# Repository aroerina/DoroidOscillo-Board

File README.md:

## Description
DroidOscillo KiCAD board data  
Schematic is here  
https://github.com/aroerina/DroidOscillo-Photos/blob/master/Schematic.pdf

## Building tools
KiCAD 4.0.2

## Parts description
U1 LPC4370FET100 - Main MCU.204MHz triple core(Cortex M4 + M0 * 2) and includes 80Msps ADC.  
U5 OPA4354 - Quad cmos opamp.  
U14 MCP4726A0T-E/CH - 12bit I2C DAC.  

## Related repositorys

DroidOscillo Firmware: https://github.com/aroerina/DroidOscillo-Firmaware  
DroidOscillo Android host: https://github.com/aroerina/DroidOscillo-Android_host  

## Wiki
https://github.com/aroerina/DroidOscillo-Android_host/wiki

## Licence

DroidOscillo Hardware is released under the [CC BY-NC 4.0](https://creativecommons.org/licenses/by-nc/4.0/)

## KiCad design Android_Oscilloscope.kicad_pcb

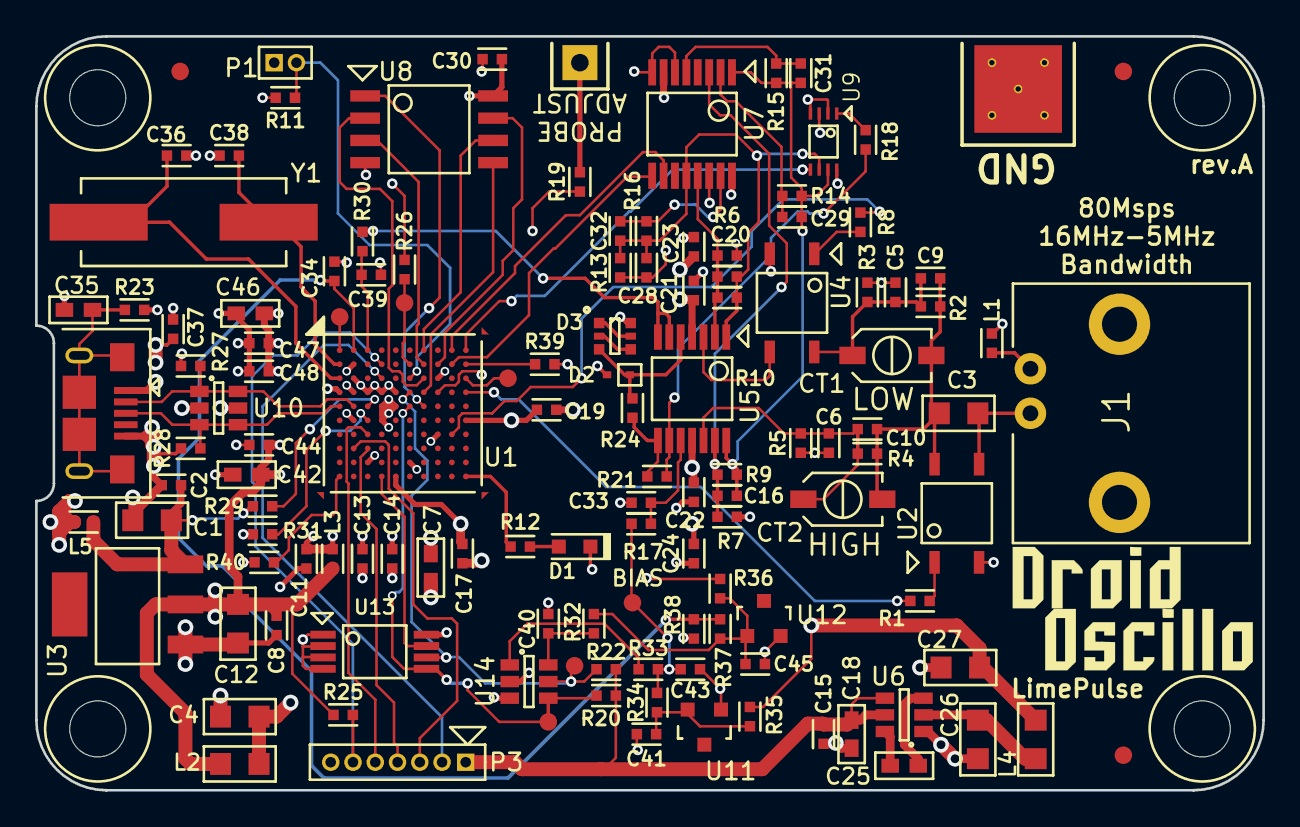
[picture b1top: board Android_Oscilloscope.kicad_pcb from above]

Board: 4 copper layers, 70.0 x 43.0 mm, 132 parts (0 on the bottom side), 77 nets.

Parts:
C1, C4, C12, C26, C27: 22u 6.3V; SMD2012
C2, C8, C11, C14, C15, C17, C19, C23, C24, C30, C33, C37, C41, C43, C44, C45, C47: 0.1u; SMD1005
C3: 47n 100V; SMD2012
C5, C32: 4.7p; SMD1005
C6: 120p; SMD1005
C7, C18, C42, C46: 10u 6.3V; SMD1608
C9, C10, C39: NM; SMD1005
C13, C48: 22n; SMD1005
C16, C20: 2.2p; SMD1005
C21, C22, C34, C40: 1u; SMD1005
C25: 4.7u 6.3V; SMD1608
C28: 15p; SMD1005
C29: 3.3p; SMD1005
C31: 10p; SMD1005
C35: 4.7n 100V; SMD1608
C36, C38: 18p; SMD1005
CT1: TZC3R100A110 3p-10p; MURATA_TZC3
CT2: TZC3Z030A110R00 1.4p-3p; MURATA_TZC3
D1: APT1608EC; SMD1608_DIODE
D2: RB521S30T5G; SOD-523
D3: BAS16VY; SOT-363
FID1: Fiducial_C; Fiducial_1mm
FID2: Fiducial_A; Fiducial_1mm
FID3: Fiducial_B; Fiducial_1mm
HOLE3MM_NC, HOLE3MM_NC#2, HOLE3MM_NC#3, HOLE3MM_NC#4: VAL**; HOLE3MM_NC
J1: BNC; BNC-R
L1, L5: BLM15AG121SN1; SMD1005
L2, L4: LBR2012T202K; SMD2012
L3: BLM15AG601SN1; SMD1005
P1: USB_BOOT; PIN_HEADER_2_1.27mm
P2: FCI_10118193-0001LF; 10118193-0001LF
P3: JTAG; PIN_HEADER_7_1.27pitch
R1, R8, R11, R36, R39, R40: 2.2k 5%; SMD1005
R2: 1100k 1%; SMD1005
R3: 910k 1%; SMD1005
R4: 1.96M 1%; SMD1005
R5: 36k 1%; SMD1005
R6, R7: 3k 1%; SMD1005
R9, R10: 27k 1%; SMD1005
R12: 10k 5%; SMD1005
R13: 3.3k 1%; SMD1005
R14: 22k 1%; SMD1005
R15: 5.6k 1%; SMD1005
R16: 13.3k 1%; SMD1005
R17, R32: 4.7k 5%; SMD1005
R18: 910 1%; SMD1005
R19, R29: 100 5%; SMD1005
R20, R22, R25, R26: 4.7k; SMD1005
R21: 1k 1%; SMD1005
R23, R27, R28: 1M 5%; SMD1005
R24: 680 1%; SMD1005
R30: 0; SMD1005
R31: 12k 1%; SMD1005
R33: 2k 1%; SMD1005
R34: 8.2k 1%; SMD1005
R35, R38: 1.5k 1%; SMD1005
R37: 2.2k 1%; SMD1005
TP1: SCL; TestPad
TP2: SDA; TestPad
TP3: RST; TestPad
U1: LPC4370FET100; TFBGA100_MYREFLOW
U2, U4: CPC1017N
U3: AMS1117-3.3; SOT-223
U5: OPA4354AIPWR; TSSOP-14_4.4x5mm_Pitch0.65mm
U6: LM2664; SOT-23-6
U7: 74HC4052PW; TSSOP-16_4.4x5mm_Pitch0.65mm
U8: W25Q80BVSSIG; SOIJ-8_5.3x5.3mm_Pitch1.27mm
U9: TC7W53FK; SSOP8_P0.5W2.3
U10: USBLC6-2SC6; SOT-23-6
U11, U12: LM385M3-1.2/NOPB; SOT-23
U13: AT24C02C-XHM-T; TSSOP-8_4.4x3mm_Pitch0.65mm
U14: MCP4726A0T-E/CH; SOT-23-6
W1: ISP; TestPad
W2: PROBE_COMP_HOLE
W3: ADC1; TestPad
W4: PROBE_GND_PAD; Probe-ADJ-GND
W5: TP_BIAS; TestPad
Y1: ABLS-12.000MHZ-B4-T; Crystal_HC49-SD_SMD

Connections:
/USB_D+: P2.3, R28.1, U1.E1, U10.3, U10.4
/USB_D-: P2.2, R27.1, U1.E2, U10.1, U10.6
/USB_VBUS: R29.1, U1.E3
ADCHS_VNEG: C39.1, R30.2, U1.A3
ADCHS_VPOS0: C34.1, R37.2, R38.1, U1.A2
BIAS: C43.2, R17.1, R33.2, R34.1, W5.1
BOOT1: R40.1, U1.K1
BOOT2: P1.2, R11.1, U1.C6
BOOT3: R39.1, U1.B10
BOOT_ISP: U1.C10, W1.1
DAC_OUT: R33.1, U14.1
DAC_VREF: C45.1, R32.1, R36.2, R37.1, U12.1
DC_SW: R1.1, U1.D10
EEPROM_WP: U1.K4, U13.7
GND: C1.2, C2.2, C4.2, C5.2, C6.2, C7.2, C8.2, C11.2, C12.2, C13.2, C14.2, C15.2, C17.2, C18.2, C19.2, C21.2, C22.1, C23.2, C24.1, C26.2, C27.2, C30.2, C33.2, C34.2, C35.2, C36.1, C37.2, C38.1, C39.2, C40.1, C41.2, C42.2, C43.1, C44.2, C45.2, C46.2, C47.2, C48.2, D1.1, D2.2, D3.6, L1.2, P2.5, P3.7, R3.1, R5.2, R6.2, R7.2, R11.2, R23.2, R27.2, R28.2, R31.2, R38.2, R39.2, R40.2, U1.C2, U1.C8, U1.D3, U1.D4, U1.D5, U1.F2, U1.G8, U1.J3, U1.J6, U2.2, U3.1, U4.2, U6.1, U7.6, U7.8, U8.4, U9.2, U9.4, U10.2, U11.1, U12.2, U13.1, U13.2, U13.3, U13.4, U14.2, W4.1
I2C_SCL: R22.2, TP1.1, U1.D6, U13.6, U14.5
I2C_SDA: R20.2, TP2.1, U1.E6, U13.5, U14.4
JTAG_RESET: P3.6, R25.2, U1.B4
JTAG_TCK: P3.3, U1.H2
JTAG_TDI: P3.5, U1.G3
JTAG_TDO: P3.4, U1.H3
JTAG_TMS: P3.2, U1.C4
LED0: R12.1, U1.K10
MUX0-S0: U1.A9, U7.10
MUX0-S1: U1.B9, U7.9
MUX1-A: U1.A10, U9.5
unnamed: C3.1, J1.C, U2.3
unnamed: C5.1, C9.2, CT1.2, R2.1, R3.2, U4.4
unnamed: C3.2, C9.1, C10.1, CT1.1, CT2.1, R2.2, R4.1, U2.4
unnamed: C6.1, C10.2, CT2.2, R4.2, R5.1, U5.12
unnamed: C7.1, C11.1, C13.1, C14.1, L3.2, U1.E4, U1.E5, U1.F4
unnamed: C16.1, C29.2, C31.2, R9.2, R14.2, R15.2, U5.14, U7.1, U9.7
unnamed: C16.2, R7.1, R9.1, U5.13, U7.3
unnamed: C20.1, R6.1, R10.2, U5.2, U7.13
unnamed: C20.2, C28.1, C32.1, R10.1, R13.1, R16.1, U5.1, U7.12, U9.6
unnamed: C25.1, U6.6
unnamed: C25.2, U6.3
unnamed: C26.1, L4.1, U6.2
unnamed: C28.2, R13.2, U7.14
unnamed: C29.1, R14.1, U7.2
unnamed: C31.1, R15.1, U7.5
unnamed: C32.2, R16.2, U7.15
unnamed: C33.1, R17.2, U5.10
unnamed: C35.1, P2.S1, P2.S2, P2.S3, P2.S4, P2.S5, P2.S6, R23.1
unnamed: C36.2, U1.C1, Y1.1
unnamed: C37.1, L5.1, P2.1, U10.5
unnamed: C38.2, U1.B1, Y1.2
unnamed: C40.2, R32.2, U14.6
unnamed: C41.1, R34.2, R35.1, U11.2
unnamed: D1.2, R12.2
unnamed: D2.1, D3.3, R24.2, U5.5
unnamed: D3.1, D3.5
unnamed: D3.2, D3.4
unnamed: J1.S, L1.1
unnamed: R1.2, U2.1
unnamed: R8.1, U4.1
unnamed: R18.1, R21.2, U5.9
unnamed: R18.2, U9.1
unnamed: R19.1, W2.1
unnamed: R21.1, R24.1, U5.8
unnamed: R26.2, TP3.1, U1.B6
unnamed: R30.1, U5.6, U5.7
unnamed: R31.1, U1.F3
unnamed: U1.A1, W3.1
unnamed: U4.3, U5.3
OP_SW: R8.2, U1.G9
PROBE_COMP: R19.2, U1.D8
SPIFI_CS: U1.E7, U8.1
SPIFI_MISO: U1.C7, U8.2
SPIFI_MOSI: U1.D7, U8.5
SPIFI_SCK: U1.A7, U8.6
SPIFI_SIO2: U1.B7, U8.3
SPIFI_SIO3: U1.B8, U8.7
VBUS: C1.1, C2.1, L5.2, R29.2, U3.3
alt_3.3VD: C8.1, C12.1, C15.1, C17.1, C18.1, C19.1, C30.1, C42.1, C44.1, C46.1, C47.1, C48.1, L2.1, L3.1, P1.1, P3.1, R20.1, R22.1, R25.1, R26.1, U1.B2, U1.D1, U1.D2, U1.F10, U1.K5, U3.2, U6.4, U6.5, U8.8, U13.8
alt_VAA+: C4.1, C21.1, C23.1, L2.2, R36.1, U5.4, U7.16, U9.8, U14.3
alt_VAA-: C22.2, C24.2, C27.1, L4.2, R35.2, U5.11, U7.7, U9.3

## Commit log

2016-12-13 1st commit
2016-12-13 add readme.md
